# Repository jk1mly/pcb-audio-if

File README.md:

# pcb-audio-if

PCからのオーデイ信号の入出力と、無線機のマイク、スピーカを接続するインタフェース
簡易的（音を検波）なVOX機能を内蔵しているのでPCからPTT制御ができない場合にも使える

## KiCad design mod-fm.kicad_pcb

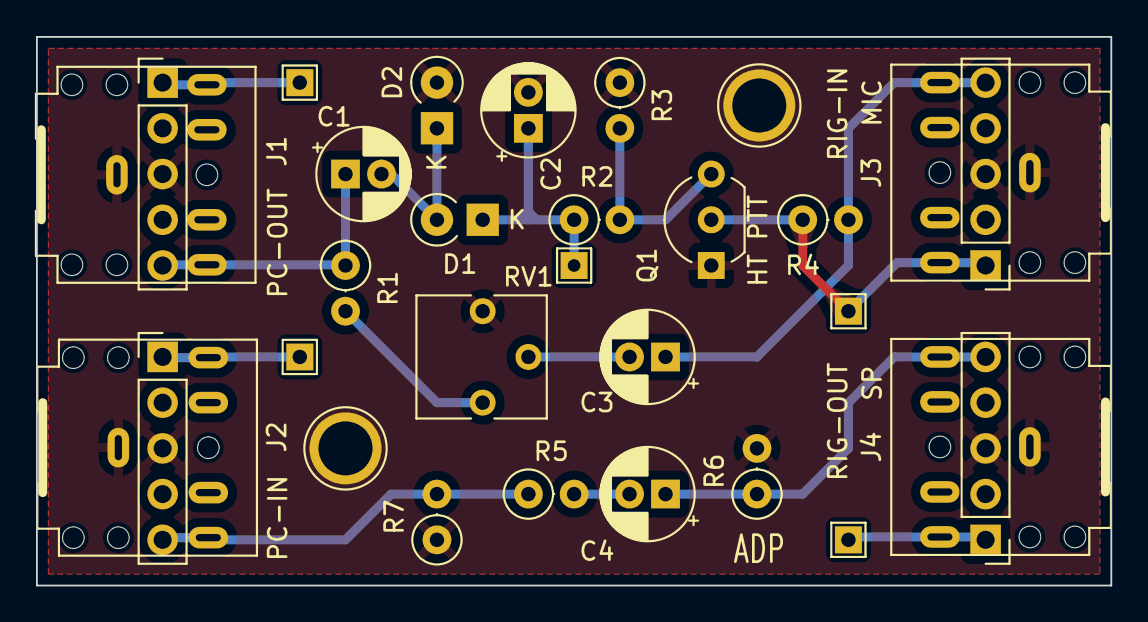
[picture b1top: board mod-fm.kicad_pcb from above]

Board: 2 copper layers, 59.7 x 30.5 mm, 30 parts (0 on the bottom side), 15 nets.

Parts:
C1, C2, C3, C4: C_Polarized; CP_Radial_D5.0mm_P2.00mm
D1, D2: Diode; D_A-405_P2.54mm_Vertical_KathodeUp
J1, J2, J3, J4: AudioJack2_Ground; Jack_3.5mm_CUI_SJ1-3525N_Horizontal
J5, J6, J7, J8: Conn_01x05_Socket; PinHeader_1x05_P2.54mm_Vertical
Q1: 2SC1815; TO-92_Inline_Wide
R1, R2, R3, R4, R5, R6, R7: R; R_Axial_DIN0207_L6.3mm_D2.5mm_P2.54mm_Vertical
RV1: R_Potentiometer_Trim; Potentiometer_Vishay_T73YP_Vertical
TP1, TP2: TestPoint; TestPoint_Plated_Hole_D3.0mm
TP3, TP4, TP5, TP6, TP7: TestPoint; TestPoint_THTPad_1.5x1.5mm_Drill0.7mm

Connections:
GND: C2.2, D2.2 (A), J1.G, J2.G, J3.G, J4.G, J5.3, J6.3, J7.3, J8.3, Q1.1 (E), R3.1, R6.2, R7.1, RV1.3, TP1.1, TP2.1
unnamed: C1.1, J1.T, R1.1
unnamed: C3.1, J3.T, R4.2
unnamed: C3.2, RV1.2
unnamed: C4.1, J4.T, R6.1
unnamed: C4.2, R5.2
unnamed: C1.2, D1.2 (A), D2.1 (K)
unnamed: C2.1, D1.1 (K), R2.1, TP7.1
unnamed: J1.S, TP3.1
unnamed: J2.S, TP4.1
unnamed: J2.T, R5.1, R7.2
unnamed: J4.S, TP5.1
unnamed: Q1.3 (B), R2.2, R3.2
unnamed: J3.S, Q1.2 (C), R4.1, TP6.1
unnamed: R1.2, RV1.1
